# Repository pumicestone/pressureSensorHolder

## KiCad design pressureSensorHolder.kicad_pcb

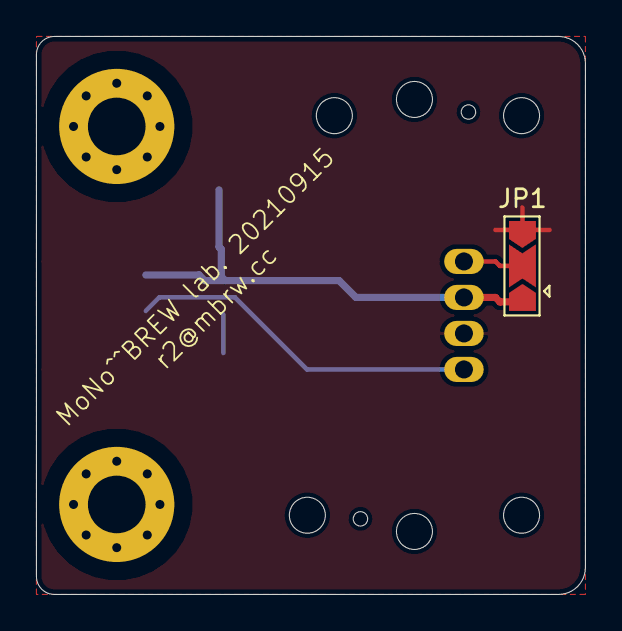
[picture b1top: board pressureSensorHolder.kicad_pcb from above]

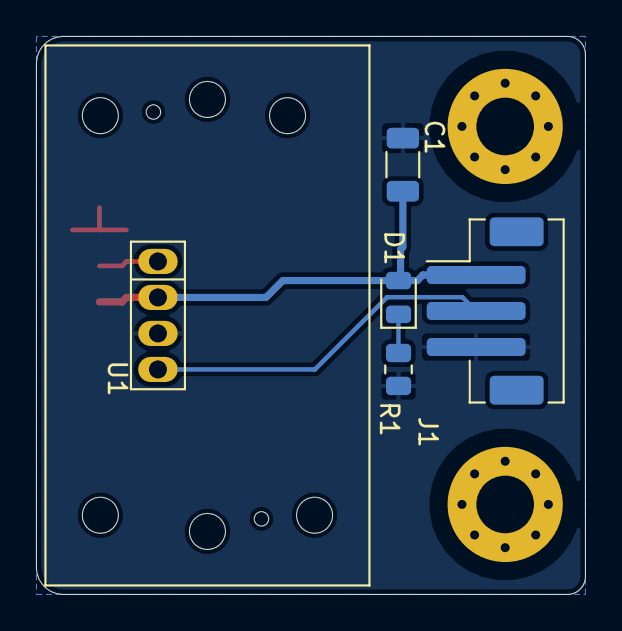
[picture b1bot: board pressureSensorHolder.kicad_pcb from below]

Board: 2 copper layers, 30.5 x 31.0 mm, 8 parts (5 on the bottom side), 5 nets.

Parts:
C1: C; C_1206_3216Metric
D1: LED; LED_0805_2012Metric
H1, H2: MountingHole; MountingHole_3.2mm_M3_Pad_Via
J1: Conn_01x03; JST_PH_B3B-PH-SM4-TB_1x03-1MP_P2.00mm_Vertical
JP1: SolderJumper_3_Open; SolderJumper-3_P2.0mm_Open_TrianglePad1.0x1.5mm
R1: 150R; R_0805_2012Metric
U1: SDP8xx-ANALOG; SDP80x

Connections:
+3V3: C1.1, D1.2, J1.1, JP1.1, U1.2
/AOut_SDA: J1.2, U1.4
/OCS_SCL: JP1.2, U1.1
GND: C1.2, J1.3, JP1.3, R1.2, U1.3
unnamed: D1.1, R1.1

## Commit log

2019-09-26 First correct version
2019-09-26 Corrected sizes
2019-10-17 First correct version + gcodes
2019-10-17 Production files
2020-12-27 New JST(PH) connection and mounting holes
2021-01-10 PCBWAY production files (20210110)
2021-03-14 Finished version for small minion housing
2021-03-29 VIA moved
2021-04-02 New socket (JST/PH-1x03) and polishing. Production files (PCBWAY)
2021-09-16 Prod. files Lenartowice
